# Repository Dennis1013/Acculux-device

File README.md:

# Acculux-device
**Capstone Project: Development of a Pressure and Navigation System For Nirscan Probe for Breast Cancer Detection**

The objective of this project is to add functionality to the existing NIR Imaging Inc. device in the way of:
 - Orientation tracking
 - Positional tracking
 - Force sensing

Download the latest software release here: https://github.com/jjhcwoo/Acculux-device/releases/latest

## Members

Justin Woo 

Allan Chang

Aodren Auffrédou-Heinicke

Dennis Huang

Nathan Cushing

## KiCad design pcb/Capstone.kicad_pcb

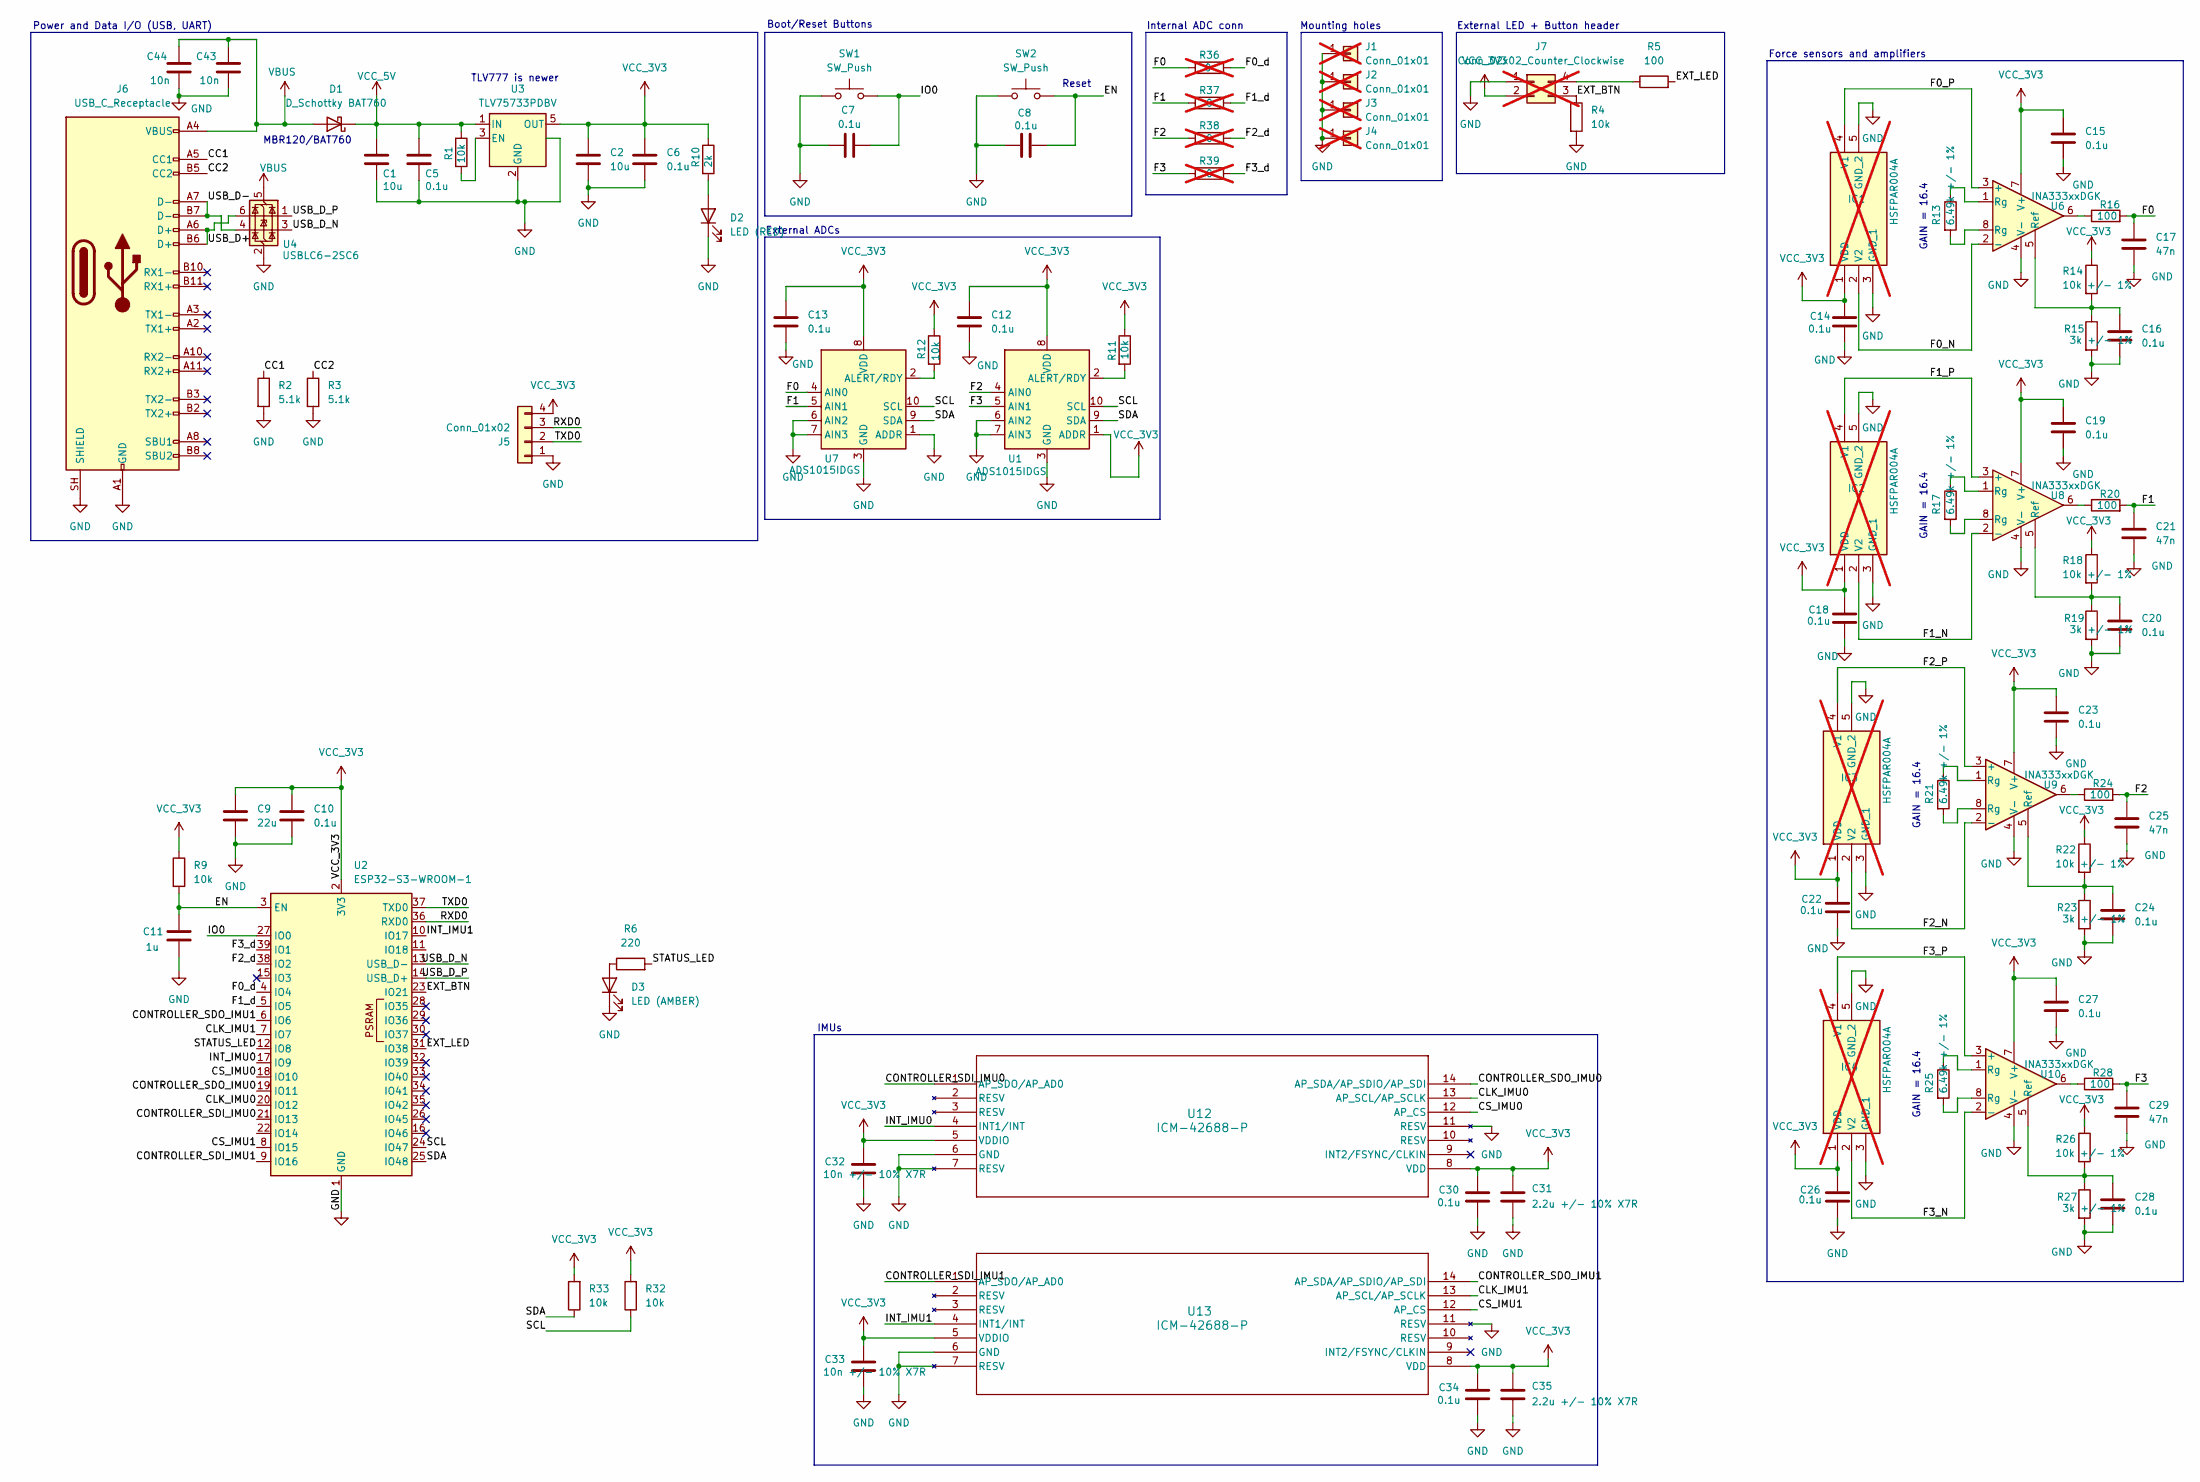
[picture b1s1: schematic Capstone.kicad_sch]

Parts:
C1, C2: 10u; C_0603_1608Metric
C5, C6, C7, C8, C10, C12, C13, C14, C15, C16, C18, C19, C20, C22, C23, C24, C26, C27, C28, C30, C34: 0.1u; C_0603_1608Metric
C9: 22u; C_0603_1608Metric
C11: 1u; C_0603_1608Metric
C17, C21, C25, C29: 47n; C_0603_1608Metric
C31, C35: 2.2u +/- 10% X7R; C_0603_1608Metric
C32, C33: 10n +/- 10% X7R; C_0603_1608Metric
C43, C44: 10n; C_0603_1608Metric
D1: D_Schottky BAT760; D_SOD-323F
D2: LED (RED); LED_0603_1608Metric
D3: LED (AMBER); LED_0603_1608Metric
IC1, IC2, IC3, IC4: HSFPAR004A; Manufacturer_Part_Number HSFPAR004A; Mouser Part Number 688-HSFPAR004A; not fitted
J1, J2, J3, J4: Conn_01x01; MountingHole_3.2mm_M3_DIN965_Pad; not fitted
J5: Conn_01x02; PinHeader_1x04_P2.54mm_Horizontal
J6: USB_C_Receptacle; USB_C_Receptacle_GCT_USB4105-xx-A_16P_TopMnt_Horizontal
J7: Conn_02x02_Counter_Clockwise; PinSocket_2x02_P2.54mm_Vertical; not fitted
R1, R4, R9, R11, R12, R32, R33: 10k; R_0603_1608Metric
R2, R3: 5.1k; R_0603_1608Metric
R5, R16, R20, R24, R28: 100; R_0603_1608Metric
R6: 220; R_0603_1608Metric
R10: 2k; R_0603_1608Metric
R13, R17, R21, R25: 6.49k +/- 1%; R_0603_1608Metric
R14, R18, R22, R26: 10k +/- 1%; R_0603_1608Metric
R15, R19, R23, R27: 3k +/- 1%; R_0603_1608Metric
R36, R37, R38, R39: 0; R_0603_1608Metric; not fitted
SW1, SW2: SW_Push; SW_SPST_EVQP7A
U1, U7: ADS1015IDGS; TSSOP-10_3x3mm_P0.5mm; Manufacturer_Part_Number ADS1015IDGSR; LCSC Part # C193969
U2: ESP32-S3-WROOM-1; Manufacturer_Part_Number ESP32-S3-WROOM-1-N4; LCSC Part # C2913197
U3: TLV75733PDBV; SOT-23-5; Manufacturer_Part_Number TLV75733PDBVR; LCSC Part # C485517
U4: USBLC6-2SC6; SOT-23-6; Manufacturer_Part_Number USBLC6-2SC6; LCSC Part # C7519
U6, U8, U9, U10: INA333xxDGK; VSSOP-8_3x3mm_P0.65mm; Manufacturer_Part_Number INA333AIDGKR; LCSC Part # C19450
U12, U13: ICM-42688-P; LGA14_2P5X3X0P91_TDK; Manufacturer_Part_Number ICM-42688-P; LCSC Part # C1850418

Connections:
/CC1: J6.A5 (CC1), R2.1
/CC2: J6.B5 (CC2), R3.1
/CLK_IMU0: U2.20 (IO12), U12.13 (AP_SCL/AP_SCLK)
/CLK_IMU1: U2.7 (IO7), U13.13 (AP_SCL/AP_SCLK)
/CONTROLLER_SDI_IMU0: U2.21 (IO13), U12.1 (AP_SDO/AP_AD0)
/CONTROLLER_SDI_IMU1: U2.9 (IO16), U13.1 (AP_SDO/AP_AD0)
/CONTROLLER_SDO_IMU0: U2.19 (IO11), U12.14 (AP_SDA/AP_SDIO/AP_SDI)
/CONTROLLER_SDO_IMU1: U2.6 (IO6), U13.14 (AP_SDA/AP_SDIO/AP_SDI)
/CS_IMU0: U2.18 (IO10), U12.12 (AP_CS)
/CS_IMU1: U2.8 (IO15), U13.12 (AP_CS)
/EN: C8.2, C11.1, R9.2, SW2.2, U2.3 (EN)
/EXT_BTN: J7.3, R4.1, U2.23 (IO21)
/EXT_LED: R5.2, U2.31 (IO38)
/F0: C17.1, R16.2, R36.2, U7.4 (AIN0)
/F0_N: IC1.2 (V2), U6.2 (-)
/F0_P: IC1.4 (V1), U6.3 (+)
/F0_d: R36.1, U2.4 (IO4)
/F1: C21.1, R20.2, R37.2, U7.5 (AIN1)
/F1_N: IC2.2 (V2), U8.2 (-)
/F1_P: IC2.4 (V1), U8.3 (+)
/F1_d: R37.1, U2.5 (IO5)
/F2: C25.1, R24.2, R38.2, U1.4 (AIN0)
/F2_N: IC3.2 (V2), U9.2 (-)
/F2_P: IC3.4 (V1), U9.3 (+)
/F2_d: R38.1, U2.38 (IO2)
/F3: C29.1, R28.2, R39.2, U1.5 (AIN1)
/F3_N: IC4.2 (V2), U10.2 (-)
/F3_P: IC4.4 (V1), U10.3 (+)
/F3_d: R39.1, U2.39 (IO1)
/INT_IMU0: U2.17 (IO9), U12.4 (INT1/INT)
/INT_IMU1: U2.10 (IO17), U13.4 (INT1/INT)
/IO0: C7.2, SW1.2, U2.27 (IO0)
/RXD0: J5.3, U2.36 (RXD0)
/SCL: R32.1, U1.10 (SCL), U2.24 (IO47), U7.10 (SCL)
/SDA: R33.1, U1.9 (SDA), U2.25 (IO48), U7.9 (SDA)
/STATUS_LED: R6.2, U2.12 (IO8)
/TXD0: J5.2, U2.37 (TXD0)
/USB_D+: J6.A6 (D+), J6.B6 (D+), U4.6 (I/O1)
/USB_D-: J6.A7 (D-), J6.B7 (D-), U4.4 (I/O2)
/USB_D_N: U2.13 (USB_D-), U4.3 (I/O2)
/USB_D_P: U2.14 (USB_D+), U4.1 (I/O1)
GND: C1.2, C2.2, C5.2, C6.2, C7.1, C8.1, C9.2, C10.2, C11.2, C12.2, C13.2, C14.2, C15.2, C16.2, C17.2, C18.2, C19.2, C20.2, C21.2, C22.2, C23.2, C24.2, C25.2, C26.2, C27.2, C28.2, C29.2, C30.2, C31.2, C32.2, C33.2, C34.2, C35.2, C43.2, C44.2, D2.1 (K), D3.1 (K), IC1.3 (GND_1), IC1.5 (GND_2), IC2.3 (GND_1), IC2.5 (GND_2), IC3.3 (GND_1), IC3.5 (GND_2), IC4.3 (GND_1), IC4.5 (GND_2), J1.1 (Pin_1_1), J2.1 (Pin_1_1), J3.1 (Pin_1_1), J4.1 (Pin_1_1), J5.1, J6.A1 (GND), J6.A12 (GND), J6.B1 (GND), J6.B12 (GND), J6.SH (SHIELD), J7.1, R2.2, R3.2, R4.2, R15.2, R19.2, R23.2, R27.2, SW1.1, SW2.1, U1.3 (GND), U1.6 (AIN2), U1.7 (AIN3), U2.1 (GND), U2.40 (GND), U2.41 (GND), U3.2 (GND), U3.4 (NC), U4.2 (GND), U6.4 (V-), U7.1 (ADDR), U7.3 (GND), U7.6 (AIN2), U7.7 (AIN3), U8.4 (V-), U9.4 (V-), U10.4 (V-), U12.6 (GND), U12.7 (RESV), U12.11 (RESV), U13.6 (GND), U13.7 (RESV), U13.11 (RESV)
unnamed: D2.2 (A), R10.2
unnamed: D3.2 (A), R6.1
unnamed: J7.4, R5.1
unnamed: R13.1, U6.1 (Rg)
unnamed: R13.2, U6.8 (Rg)
unnamed: R16.1, U6.6
unnamed: R17.1, U8.1 (Rg)
unnamed: R17.2, U8.8 (Rg)
unnamed: R20.1, U8.6
unnamed: R21.1, U9.1 (Rg)
unnamed: R21.2, U9.8 (Rg)
unnamed: R24.1, U9.6
unnamed: R25.1, U10.1 (Rg)
unnamed: R25.2, U10.8 (Rg)
unnamed: R28.1, U10.6
unnamed: R11.2, U1.2 (ALERT/RDY)
unnamed: R1.2, U3.3 (EN)
unnamed: C16.1, R14.2, R15.1, U6.5 (Ref)
unnamed: R12.2, U7.2 (ALERT/RDY)
unnamed: C20.1, R18.2, R19.1, U8.5 (Ref)
unnamed: C24.1, R22.2, R23.1, U9.5 (Ref)
unnamed: C28.1, R26.2, R27.1, U10.5 (Ref)
VBUS: C43.1, C44.1, D1.2 (A), J6.A4 (VBUS), J6.A9 (VBUS), J6.B4 (VBUS), J6.B9 (VBUS), U4.5 (VBUS)
VCC_3V3: C2.1, C6.1, C9.1, C10.1, C12.1, C13.1, C14.1, C15.1, C18.1, C19.1, C22.1, C23.1, C26.1, C27.1, C30.1, C31.1, C32.1, C33.1, C34.1, C35.1, IC1.1 (VDD), IC2.1 (VDD), IC3.1 (VDD), IC4.1 (VDD), J5.4, J7.2, R9.1, R10.1, R11.1, R12.1, R14.1, R18.1, R22.1, R26.1, R32.2, R33.2, U1.1 (ADDR), U1.8 (VDD), U2.2 (3V3), U3.5 (OUT), U6.7 (V+), U7.8 (VDD), U8.7 (V+), U9.7 (V+), U10.7 (V+), U12.5 (VDDIO), U12.8 (VDD), U13.5 (VDDIO), U13.8 (VDD)
VCC_5V: C1.1, C5.1, D1.1 (K), R1.1, U3.1 (IN)

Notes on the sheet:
Internal ADC conn
External ADCs
Force sensors and amplifiers
GAIN = 16.4
IMUs
MBR120/BAT760
TLV777 is newer
Boot/Reset Buttons
Reset
External LED + Button header
Power and Data I/O (USB, UART)
Mounting holes

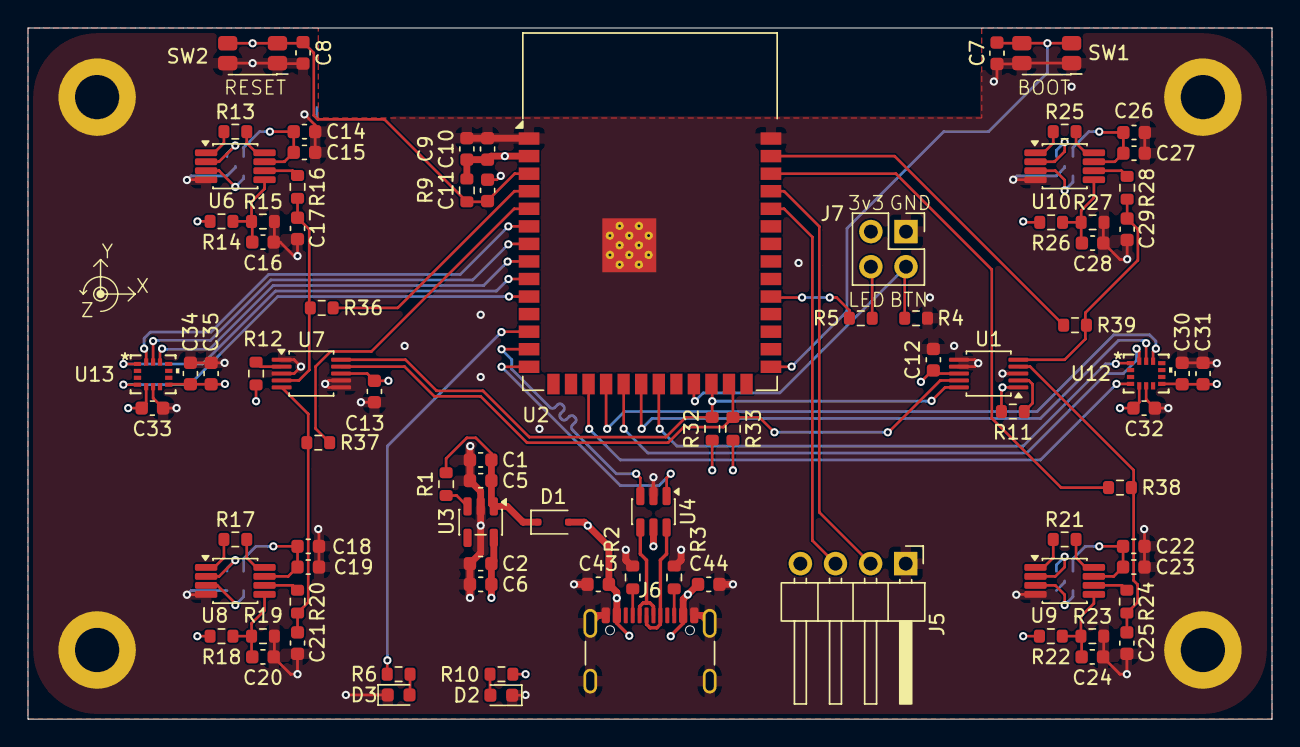
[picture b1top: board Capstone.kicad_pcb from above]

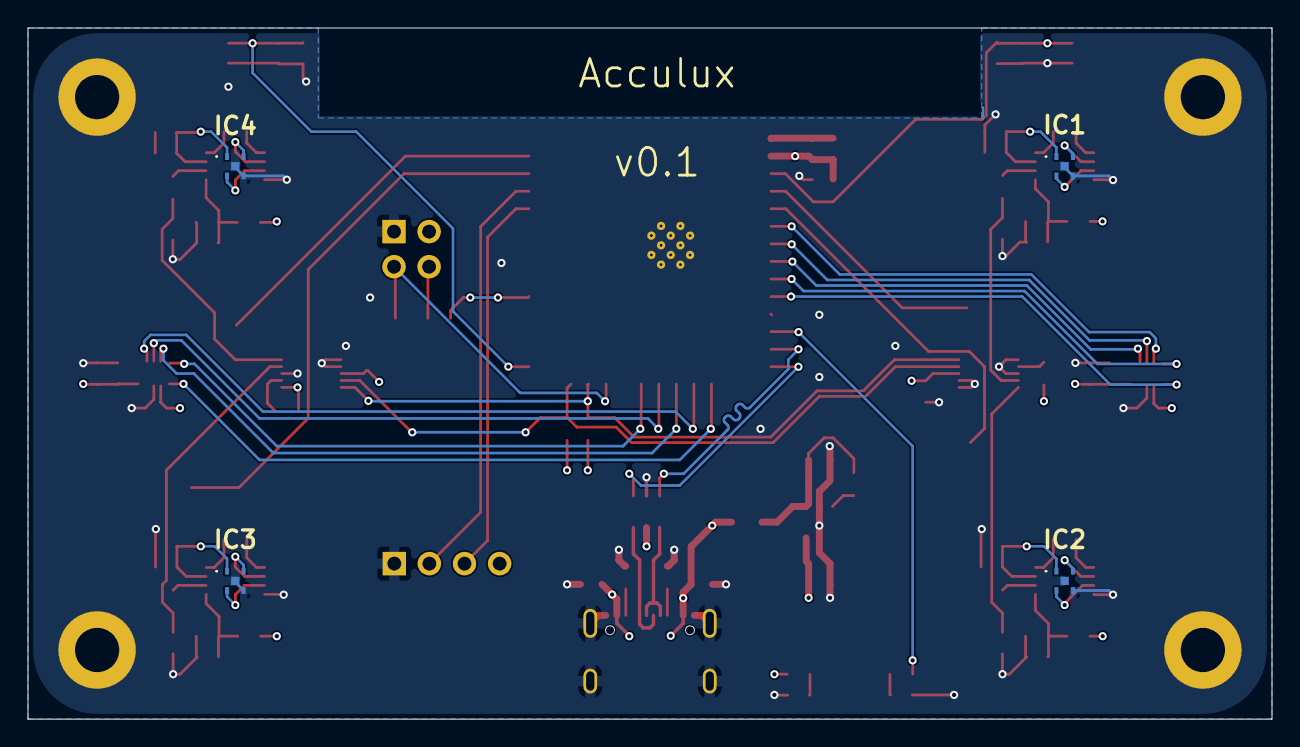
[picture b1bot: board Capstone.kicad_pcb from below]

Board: 4 copper layers, 90.0 x 50.0 mm, 94 parts (4 on the bottom side), 67 nets.
